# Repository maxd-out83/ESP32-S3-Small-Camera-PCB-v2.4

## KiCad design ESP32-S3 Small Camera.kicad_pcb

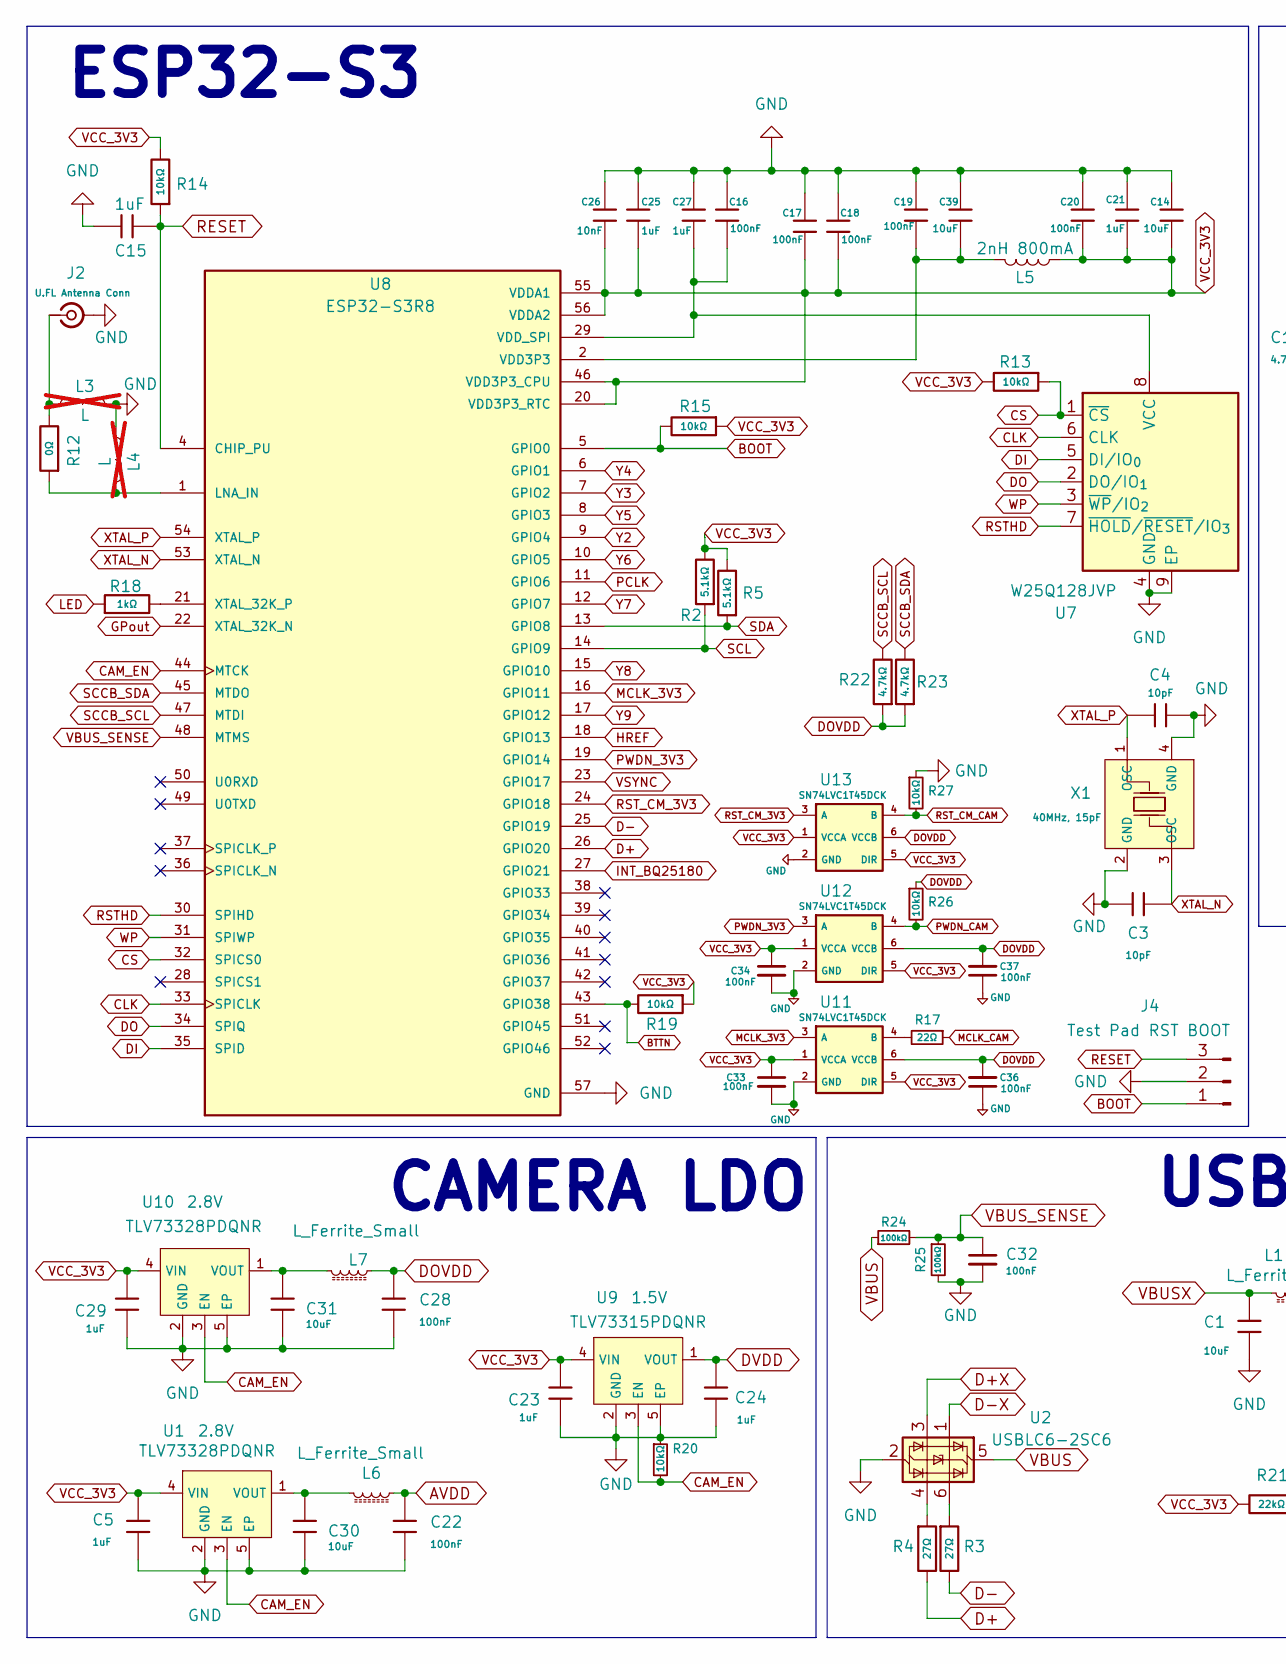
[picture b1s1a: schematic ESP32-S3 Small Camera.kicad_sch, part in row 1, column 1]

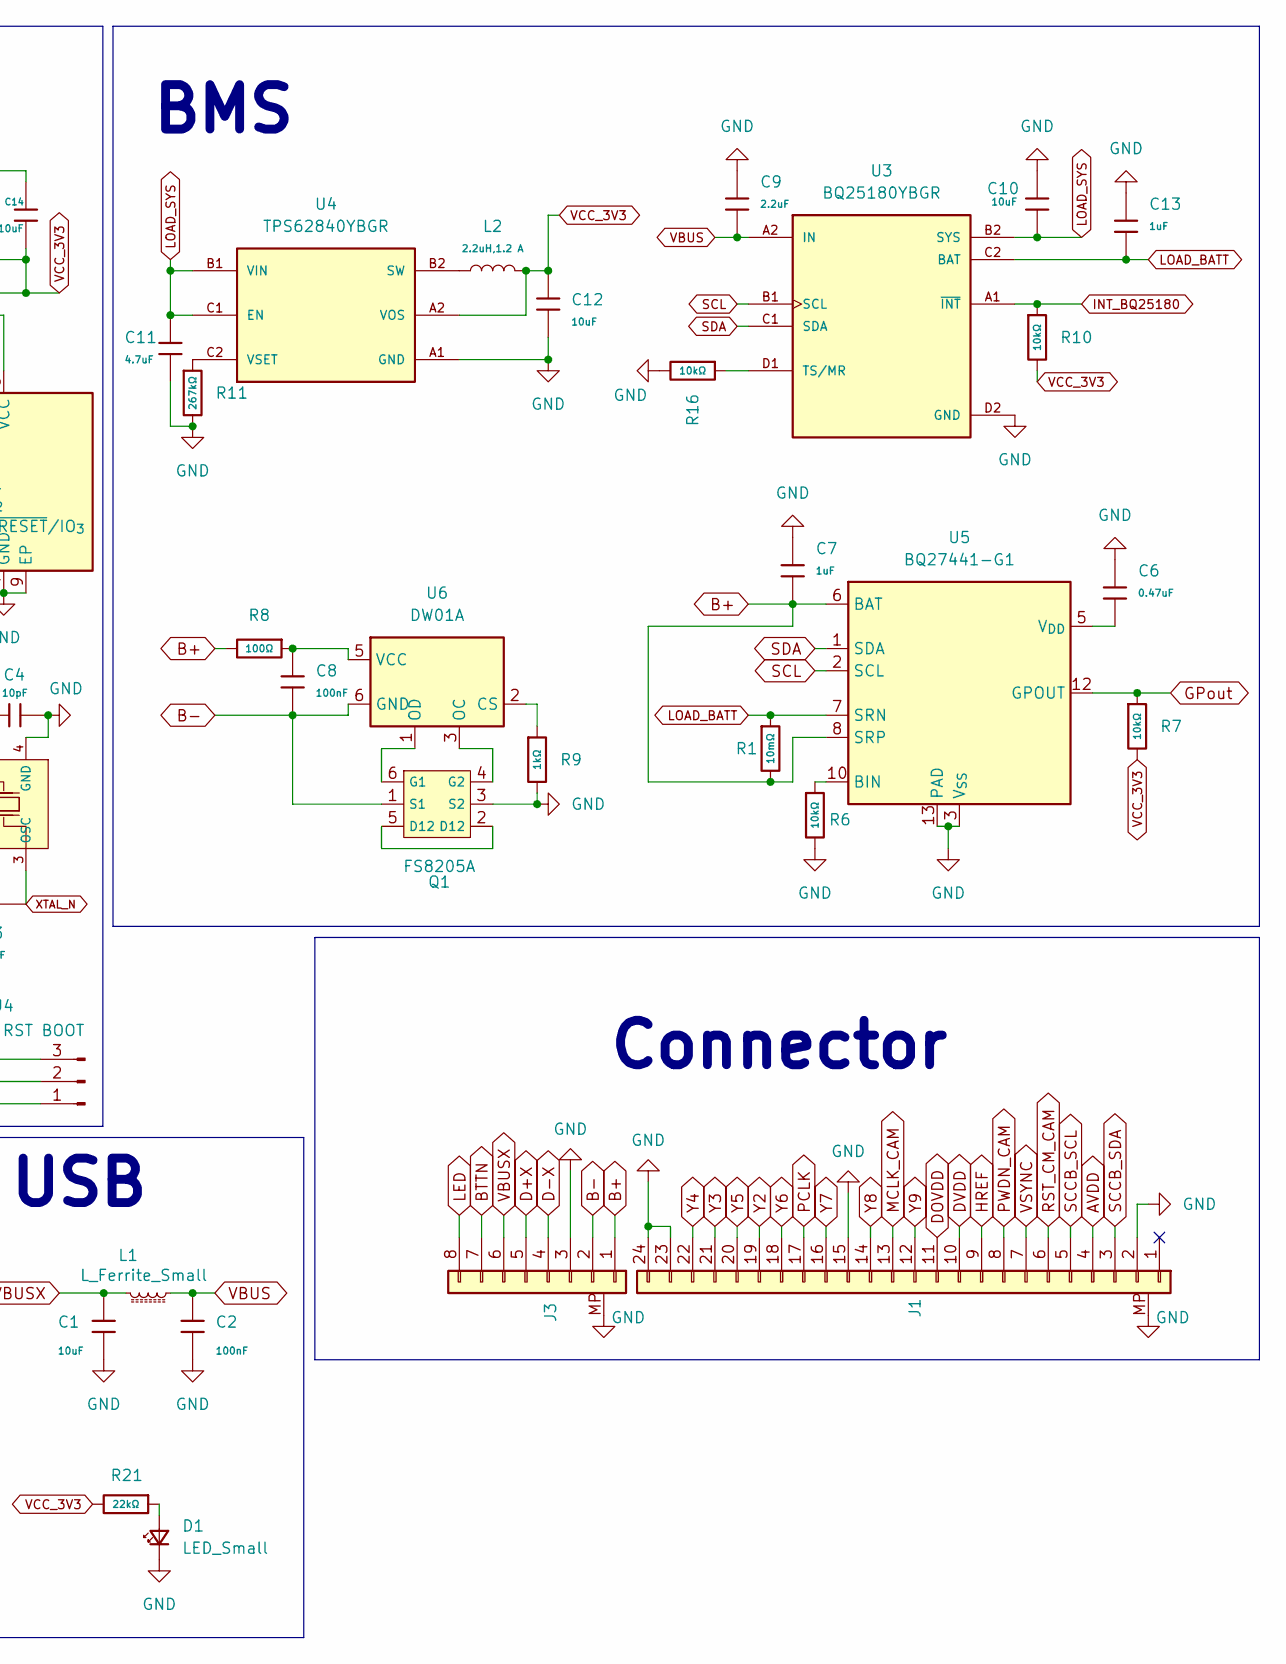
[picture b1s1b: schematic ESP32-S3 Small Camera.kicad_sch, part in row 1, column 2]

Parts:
C1, C10, C12, C14, C30, C31, C39: 10uF; C_0402; LCSC C15525
C2, C8, C16, C17, C18, C19, C20, C22, C28, C32, C33, C34, C36, C37: 100nF; C_0201_0603Metric; LCSC C18164586
C3, C4: 10pF; C_0402_1005Metric; LCSC C32949
C5, C7, C13, C15, C21, C23, C24, C25, C27, C29: 1uF; C_0201_0603Metric; LCSC C53067
C6: 0.47uF; C_0201_0603Metric; LCSC C318543
C9: 2.2uF; C_0201_0603Metric; LCSC C77762
C11: 4.7uF; C_0402; LCSC C23733
C26: 10nF; C_0201_0603Metric; LCSC C526939
D1: LED_Small; LED_0603_1608Metric; LCSC C2286
J1: Conn_01x24; XUNPU_FPC-05F-24PH20_1x24-1MP_P0.5mm_Horizontal; LCSC C2856805
J2: U.FL Antenna Conn; U.FL_Hirose_U.FL-R-SMT-1_Vertical; LCSC C88373
J3: Conn_01x08; JST_SH_SM08B-SRSS-TB_1x08-1MP_P1.00mm_Horizontal; LCSC C160407
J4: Test Pad RST BOOT; TestPoint_Pad_1.0x1.0mm
L1, L6, L7: L_Ferrite_Small; L_0603_1608Metric; LCSC C85833
L2: 2.2uH,1.2 A; L_0805; LCSC C2049745
L3, L4: L; C_0201_0603Metric; not fitted
L5: 2nH 800mA; L_0402_1005Metric; LCSC C3032791
Q1: FS8205A; SOT-23-6; LCSC C908265
R1: 10mΩ; R_0805_2012Metric; LCSC C236283
R2, R5: 5.1kΩ; R_0201_0603Metric; LCSC C270344
R3, R4: 27Ω; R_0201_0603Metric; LCSC C270320
R6, R7, R10, R13, R14, R15, R16, R19, R20, R26, R27: 10kΩ; R_0201_0603Metric; LCSC C473048
R8: 100Ω; R_0402; LCSC C25076
R9, R18: 1kΩ; R_0402; LCSC C11702
R11: 267kΩ; R_0201_0603Metric; LCSC C423627
R12: 0Ω; C_0201_0603Metric; LCSC C270337
R17: 22Ω; R_0201_0603Metric; LCSC C270355
R21: 22kΩ; R_0402_1005Metric; LCSC C25768
R22, R23: 4.7kΩ; R_0201_0603Metric; LCSC C25900
R24, R25: 100kΩ; R_0201_0603Metric; LCSC C25741
U1, U10: TLV73328PDQNR; X2SON-4-EP-1x1; LCSC C2867701
U2: USBLC6-2SC6; SOT-23-6; LCSC C7519
U3: BQ25180YBGR; IC_BQ25180YBGR; LCSC C3682423
U4: TPS62840YBGR; TPS62840; LCSC C2071139
U5: BQ27441-G1; Texas_S-PDSO-N12; LCSC C473397
U6: DW01A; SOT-23-6; LCSC C42380662
U7: W25Q128JVP; WSON-8-1EP_6x5mm_P1.27mm_EP3.4x4.3mm; LCSC C190862
U8: ESP32-S3R8; LCSC C2913194
U9: TLV73315PDQNR; X2SON-4-EP-1x1; LCSC C2867302
U11, U12, U13: SN74LVC1T45DCK; SOT-363_SC-70-6; LCSC C9382
X1: 40MHz, 15pF; Crystal_SMD_2016-4Pin_2.0x1.6mm; LCSC C424432

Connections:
AVDD: C22.1, J1.4, L6.1
B+: C7.2, J3.1, R1.2, R8.2, U5.6 (BAT), U5.8 (SRP)
B-: C8.2, J3.2, Q1.1 (S1), U6.6 (GND)
BOOT: J4.1, R15.2, U8.5 (GPIO0)
BTTN: J3.7, R19.2, U8.43 (GPIO38)
CAM_EN: R20.2, U1.3 (EN), U8.44 (MTCK), U9.3 (EN), U10.3 (EN)
CLK: U7.6 (CLK), U8.33 (SPICLK)
CS: R13.1, U7.1 (~CS), U8.32 (SPICS0)
D+: R4.2, U8.26 (GPIO20)
D+X: J3.5, U2.3 (I/O2)
D-: R3.2, U8.25 (GPIO19)
D-X: J3.4, U2.1 (I/O1)
DI: U7.5 (DI/IO_{0}), U8.35 (SPID)
DO: U7.2 (DO/IO_{1}), U8.34 (SPIQ)
DOVDD: C28.1, C36.2, C37.2, J1.11, L7.1, R22.1, R23.1, R26.1, U11.6 (VCCB), U12.6 (VCCB), U13.6 (VCCB)
DVDD: C24.1, J1.10, U9.1 (VOUT)
GND: C1.2, C2.2, C3.1, C4.1, C5.2, C6.1, C7.1, C9.1, C10.1, C11.2, C12.2, C13.1, C14.1, C15.2, C16.1, C17.1, C18.1, C19.1, C20.1, C21.1, C22.2, C23.2, C24.2, C25.1, C26.1, C27.1, C28.2, C29.2, C30.2, C31.2, C32.2, C33.2, C34.2, C36.1, C37.1, C39.1, D1.1 (K), J1.2, J1.15, J1.23, J1.24, J1.MP, J2.2 (Ext), J3.3, J3.MP, J4.2, L3.2, L4.1, Q1.3 (S2), R6.2, R9.2, R11.2, R16.2, R20.1, R25.2, R27.1, U1.2 (GND), U1.5 (EP), U2.2 (GND), U3.D2 (GND), U4.A1 (GND), U5.3 (V_{SS}), U5.13 (PAD), U7.4 (GND), U7.9 (EP), U8.57 (GND), U9.2 (GND), U9.5 (EP), U10.2 (GND), U10.5 (EP), U11.2 (GND), U12.2 (GND), U13.2 (GND), X1.2 (GND), X1.4 (GND)
GPout: R7.1, U5.12 (GPOUT), U8.22 (XTAL_32K_N)
HREF: J1.9, U8.18 (GPIO13)
INT_BQ25180: R10.1, U3.A1 (~INT), U8.27 (GPIO21)
LED: J3.8, R18.1
LOAD_BATT: C13.2, R1.1, U3.C2 (BAT), U5.7 (SRN)
LOAD_SYS: C10.2, C11.1, U3.B2 (SYS), U4.B1 (VIN), U4.C1 (EN)
MCLK_3V3: U8.16 (GPIO11), U11.3 (A)
MCLK_CAM: J1.13, R17.1
unnamed: D1.2 (A), R21.1
unnamed: J2.1 (In), L3.1, R12.2
unnamed: Q1.2 (D12), Q1.5 (D12)
unnamed: Q1.6 (G1), U6.1 (OD)
unnamed: Q1.4 (G2), U6.3 (OC)
unnamed: R3.1, U2.6 (I/O1)
unnamed: R4.1, U2.4 (I/O2)
unnamed: C30.1, L6.2, U1.1 (VOUT)
unnamed: R16.1, U3.D1 (TS/MR)
unnamed: L2.1, U4.B2 (SW)
unnamed: R11.1, U4.C2 (VSET)
unnamed: R6.1, U5.10 (BIN)
unnamed: C6.2, U5.5 (V_{DD})
unnamed: R9.1, U6.2 (CS)
unnamed: C8.1, R8.1, U6.5 (VCC)
unnamed: C16.2, C27.2, U7.8 (VCC), U8.29 (VDD_SPI)
unnamed: L4.2, R12.1, U8.1 (LNA_IN)
unnamed: R18.2, U8.21 (XTAL_32K_P)
unnamed: C31.1, L7.2, U10.1 (VOUT)
unnamed: R17.2, U11.4 (B)
PCLK: J1.17, U8.11 (GPIO6)
PWDN_3V3: U8.19 (GPIO14), U12.3 (A)
PWDN_CAM: J1.8, R26.2, U12.4 (B)
RESET: C15.1, J4.3, R14.1, U8.4 (CHIP_PU)
RSTHD: U7.7 (~HOLD/~RESET/IO_{3}), U8.30 (SPIHD)
RST_CM_3V3: U8.24 (GPIO18), U13.3 (A)
RST_CM_CAM: J1.6, R27.2, U13.4 (B)
SCCB_SCL: J1.5, R22.2, U8.47 (MTDI)
SCCB_SDA: J1.3, R23.2, U8.45 (MTDO)
SCL: R2.1, U3.B1 (SCL), U5.2 (SCL), U8.14 (GPIO9)
SDA: R5.1, U3.C1 (SDA), U5.1 (SDA), U8.13 (GPIO8)
VBUS: C2.1, C9.2, L1.1, R24.1, U2.5 (VBUS), U3.A2 (IN)
VBUSX: C1.1, J3.6, L1.2
VBUS_SENSE: C32.1, R24.2, R25.1, U8.48 (MTMS)
VCC_3V3: C5.1, C12.1, C14.2, C17.2, C18.2, C20.2, C21.2, C23.1, C25.2, C26.2, C29.1, C33.1, C34.1, L2.2, L5.1, R2.2, R5.2, R7.2, R10.2, R13.2, R14.2, R15.1, R19.1, R21.2, U1.4 (VIN), U4.A2 (VOS), U8.20 (VDD3P3_RTC), U8.46 (VDD3P3_CPU), U8.55 (VDDA1), U8.56 (VDDA2), U9.4 (VIN), U10.4 (VIN), U11.1 (VCCA), U11.5 (DIR), U12.1 (VCCA), U12.5 (DIR), U13.1 (VCCA), U13.5 (DIR)
VDD3P3: C19.2, C39.2, L5.2, U8.2 (VDD3P3), U8.3 (VDD3P3)
VSYNC: J1.7, U8.23 (GPIO17)
WP: U7.3 (~WP/IO_{2}), U8.31 (SPIWP)
XTAL_N: C3.2, U8.53 (XTAL_N), X1.3 (OSC)
XTAL_P: C4.2, U8.54 (XTAL_P), X1.1 (OSC)
Y2: J1.19, U8.9 (GPIO4)
Y3: J1.21, U8.7 (GPIO2)
Y4: J1.22, U8.6 (GPIO1)
Y5: J1.20, U8.8 (GPIO3)
Y6: J1.18, U8.10 (GPIO5)
Y7: J1.16, U8.12 (GPIO7)
Y8: J1.14, U8.15 (GPIO10)
Y9: J1.12, U8.17 (GPIO12)

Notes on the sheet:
BMS
ESP32-S3
USB
Connector
CAMERA LDO

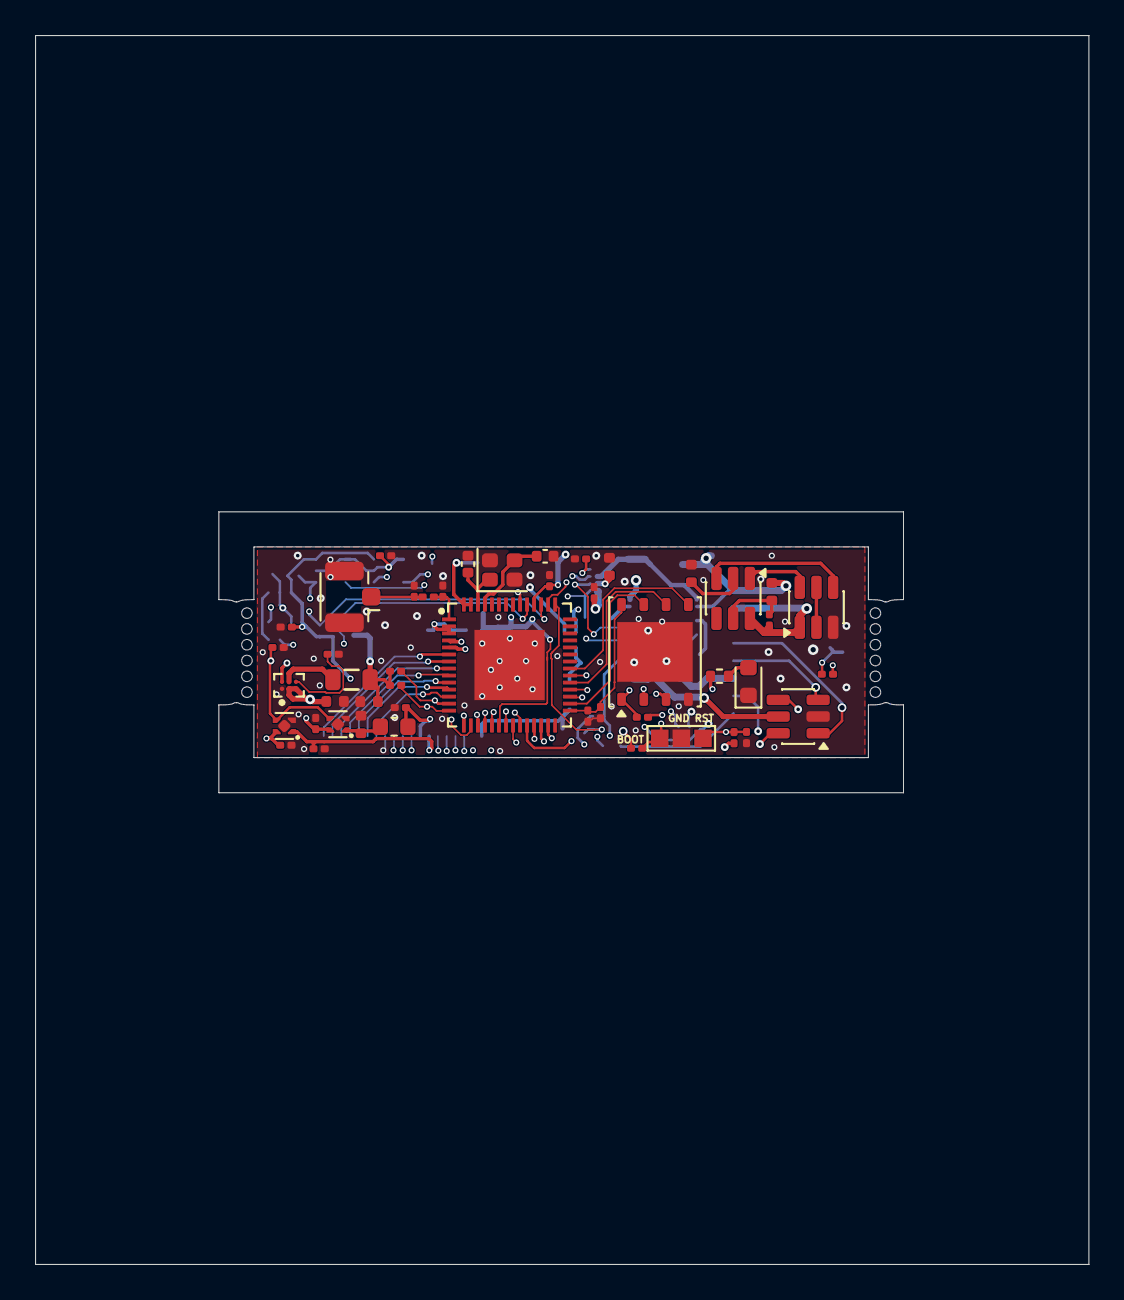
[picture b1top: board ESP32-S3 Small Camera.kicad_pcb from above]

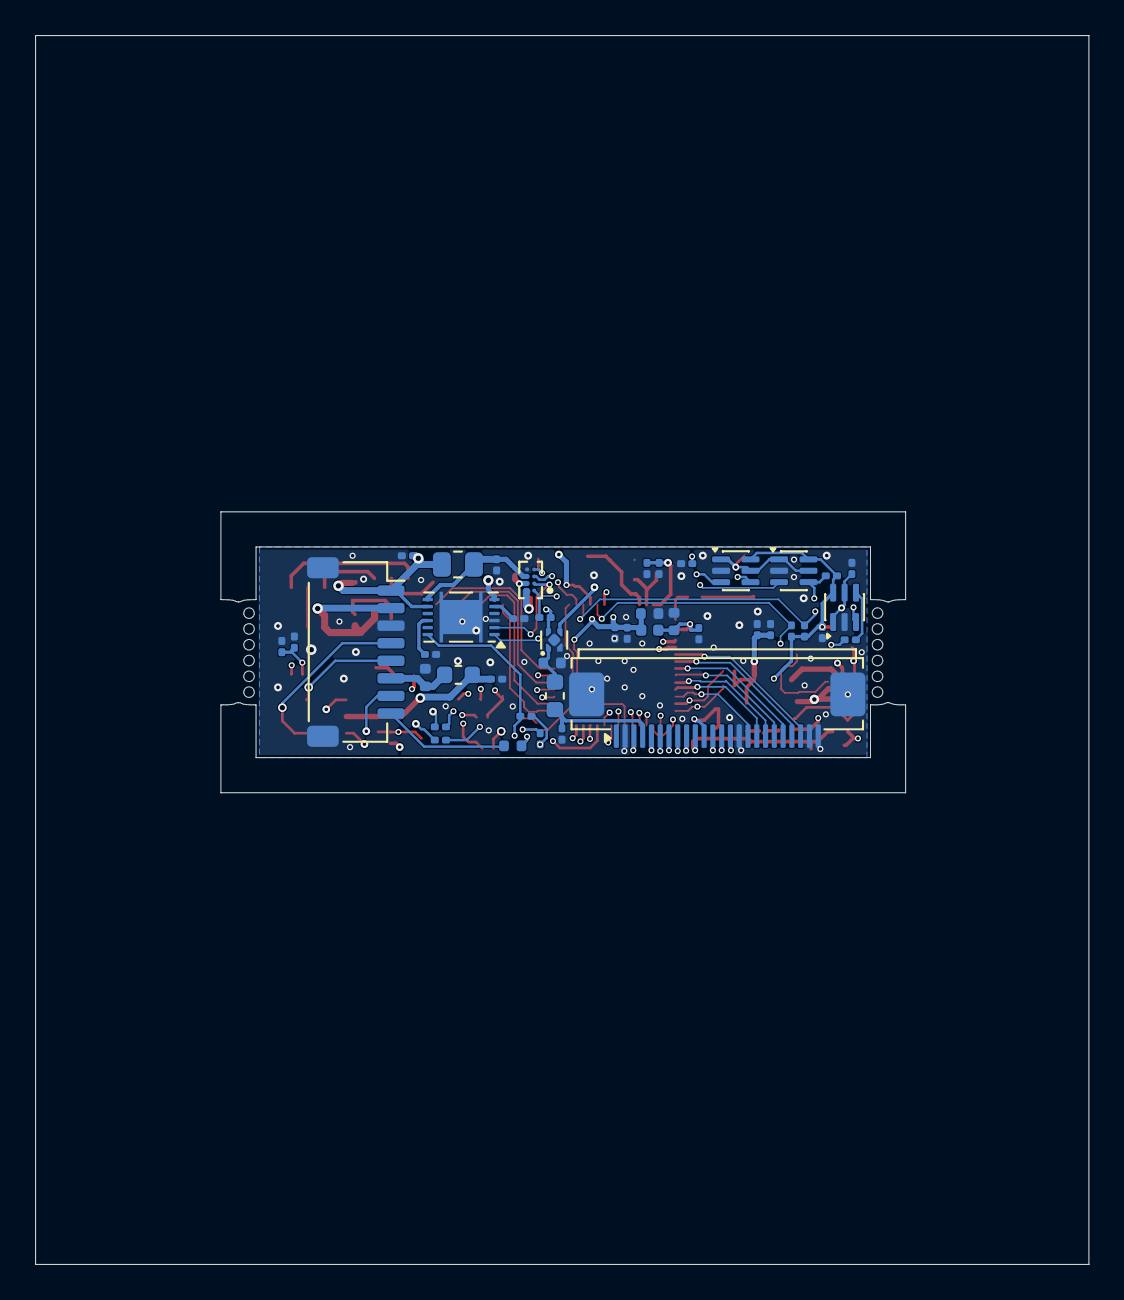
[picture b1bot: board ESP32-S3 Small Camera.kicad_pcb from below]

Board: 8 copper layers, 60.0 x 70.0 mm, 91 parts (44 on the bottom side), 73 nets.

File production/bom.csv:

Designator,Footprint,Quantity,Value,LCSC Part #
"C1, C10, C12, C14, C30, C31, C39",C_0402,7,10uF,C15525
C11,C_0402,1,4.7uF,C23733
"C13, C15, C21, C23, C24, C25, C27, C29, C5, C7",0201,10,1uF,C53067
"C16, C17, C18, C19, C2, C20, C22, C28, C32, C33, C34, C36, C37, C8",0201,14,100nF,C18164586
C26,0201,1,10nF,C526939
"C3, C4",0402,2,10pF,C32949
C6,0201,1,0.47uF,C318543
C9,0201,1,2.2uF,C77762
D1,0603,1,LED_Small,C2286
J1,XUNPU_FPC-05F-24PH20_1x24-1MP_P0.5mm_Horizontal,1,Conn_01x24,C2856805
J2,U.FL_Hirose_U.FL-R-SMT-1_Vertical,1,U.FL Antenna Conn,C88373
J3,JST_SH_SM08B-SRSS-TB_1x08-1MP_P1.00mm_Horizontal,1,Conn_01x08,C160407
"L1, L6, L7",0603,3,L_Ferrite_Small,C85833
L2,L_0805,1,"2.2uH,1.2 A",C2049745
L5,0402,1,2nH 800mA,C3032791
Q1,SOT-23-6,1,FS8205A,C908265
R1,0805,1,10mΩ,C236283
"R10, R13, R14, R15, R16, R19, R20, R26, R27, R6, R7",0201,11,10kΩ,C473048
R11,0201,1,267kΩ,C423627
R12,0201,1,0Ω,C270337
R17,0201,1,22Ω,C270355
"R18, R9",R_0402,2,1kΩ,C11702
"R2, R5",0201,2,5.1kΩ,C270344
R21,0402,1,22kΩ,C25768
"R22, R23",0201,2,4.7kΩ,C25900
"R24, R25",0201,2,100kΩ,C25741
"R3, R4",0201,2,27Ω,C270320
R8,R_0402,1,100Ω,C25076
"U1, U10",X2SON-4-EP-1x1,2,TLV73328PDQNR,C2867701
"U11, U12, U13",SOT-363_SC-70-6,3,SN74LVC1T45DCK,C9382
U2,SOT-23-6,1,USBLC6-2SC6,C7519
U3,IC_BQ25180YBGR,1,BQ25180YBGR,C3682423
U4,TPS62840,1,TPS62840YBGR,C2071139
U5,Texas_S-PDSO-N12,1,BQ27441-G1,C473397
U6,SOT-23-6,1,DW01A,C42380662
U7,WSON-8-1EP_6x5mm_P1.27mm_EP3.4x4.3mm,1,W25Q128JVP,C190862
U8,ESP32-S3R8,1,ESP32-S3R8,C2913194
U9,X2SON-4-EP-1x1,1,TLV73315PDQNR,C2867302
X1,Crystal_SMD_2016-4Pin_2.0x1.6mm,1,"40MHz, 15pF",C424432
